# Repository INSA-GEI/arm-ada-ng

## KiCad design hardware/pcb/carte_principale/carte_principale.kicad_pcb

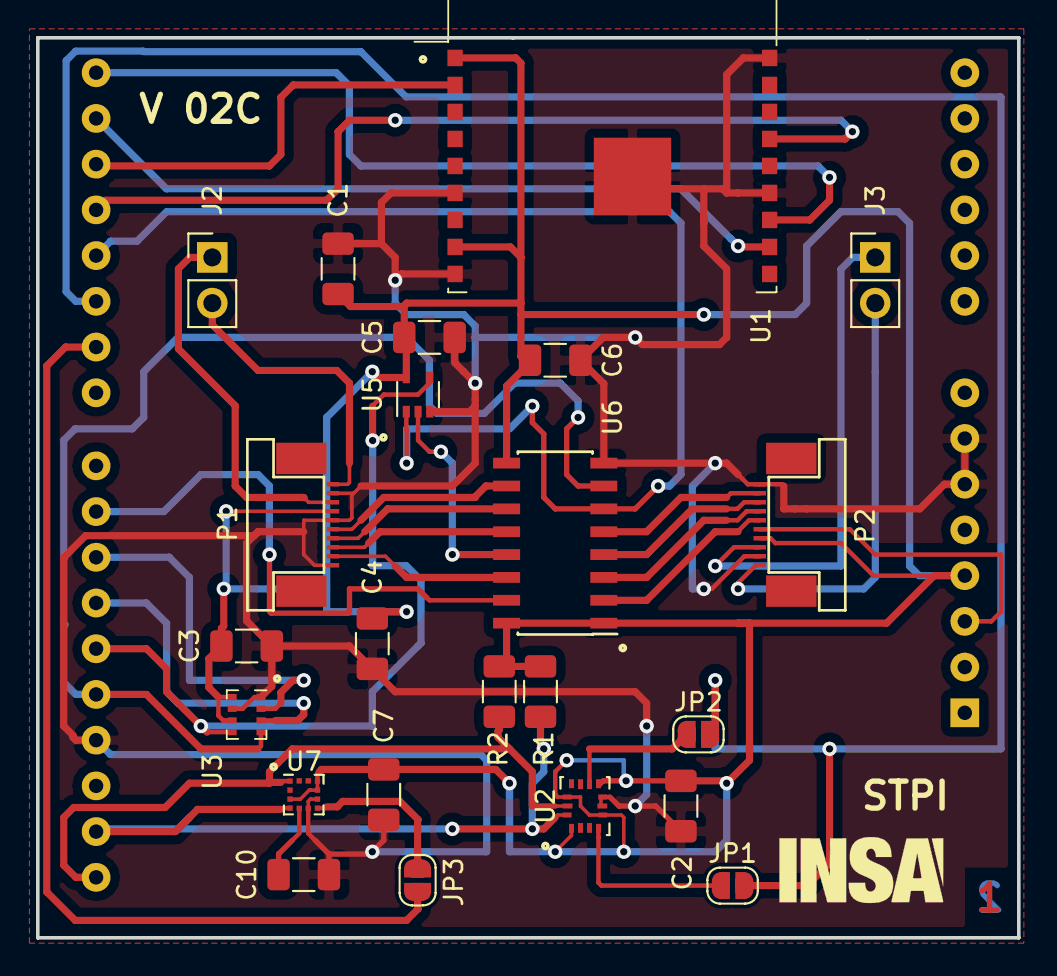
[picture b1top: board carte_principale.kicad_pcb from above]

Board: 2 copper layers, 54.5 x 50.0 mm, 25 parts (1 on the bottom side), 34 nets.

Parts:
C1, C2, C3, C4, C5, C6, C7: 100nF; C_1206_3216Metric
C10: 220nF; C_1206_3216Metric
J1: Arduino_UNO_R3; Arduino_UNO_R3_Pin_Only
J2, J3: Conn_01x02; PinHeader_1x02_P2.54mm_Vertical
JP1, JP2, JP3: SJ; SolderJumper-2_P1.3mm_Open_RoundedPad1.0x1.5mm
Logo1: LOGO; insa-image
P1, P2: TE-FFC-10-0.5; FFC-10-0.5
R1, R2: 10K; R_1206_3216Metric
U1: ESP-WROOM-02
U2: LSM6DS3; LGA-14_3x2.5mm_P0.5mm_LayoutBorder3x4y-slim
U3: BMP280; Bosch_LGA-8_2x2.5mm_P0.65mm_ClockwisePinNumbering
U5: 74AHC1G125; SOT-353_SC-70-5
U6: 74LS166; SOIC-16_3.9x9.9mm_P1.27mm
U7: LIS2MDL; LGA-12_2x2mm_P0.5mm-slim

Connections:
/Audio_Left_1: J2.2, P1.10
/Audio_Left_2: J2.1, P1.8
/Audio_Right_1: J3.2, P2.10
/Audio_Right_2: J3.1, P2.8
/BMP280_EN: J1.25, U3.2
/I2C_SCL: J1.32, R2.2, U2.13, U7.1
/I2C_SDA: J1.31, R1.2, U2.14, U7.4
/KEYS_EN: J1.19, U5.1, U6.6
/KEYS_LOAD: J1.24, U6.15
/KEY_RST: J1.3, P2.6
/Key_A: P2.4, U6.3
/Key_B: P2.5, U6.2
/Key_Down: P1.2, U6.14
/Key_Left: P1.5, U6.10
/Key_Right: P1.4, U6.11
/Key_Up: P1.3, U6.12
/Key_X: P2.2, U6.5
/Key_Y: P2.3, U6.4
/LIS2MDL_IT: J1.21, JP3.1
/LSM6DS3_IT: J1.20, JP1.2, JP2.2
/SPI_MISO: J1.27, U3.5, U5.4
/SPI_MOSI: J1.26, U3.3
/SPI_SCK: J1.28, U3.4, U6.7
/WIFI_EN: J1.17, U1.2
/WIFI_RST: J1.18, U1.15
/WIFI_RX: J1.16, U1.11
/WIFI_TX: J1.15, U1.12
GND: C1.2, C2.2, C3.2, C4.2, C5.2, C6.2, C7.2, C10.2, J1.6, J1.7, J1.29, P1.1, P1.6, P1.9, P2.1, P2.9, U1.6, U1.9, U1.13, U1.18, U1.19, U2.6, U2.7, U3.1, U3.7, U5.3, U6.8, U7.6, U7.8
unnamed: C10.1, U7.5
unnamed: JP1.1, U2.4
unnamed: JP2.1, U2.9
unnamed: JP3.2, U7.7
unnamed: U5.2, U6.13
VCC: C1.1, C2.1, C3.1, C4.1, C5.1, C6.1, C7.1, J1.4, P1.7, P2.7, R1.1, R2.1, U1.1, U1.8, U2.1, U2.5, U2.8, U2.12, U3.6, U3.8, U5.5, U6.1, U6.9, U6.16, U7.3, U7.9, U7.10

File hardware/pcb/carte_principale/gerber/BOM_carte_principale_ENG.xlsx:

Part | Value | Device | Package | Description | Description2 | Qty | Place_YES/NO | Provided_by_customer_YES/NO | Distributor | Ordernumber | Weblink | Remarks_customer | Unit_price | Total_price | REMARKS_BETA | OPTION1 | OPTION2 | OPTION3
C3,C2,C7,C6,C1,C5,C4 | 100nF | C1206C104M5RACTU | 1206 | Capacitor, 100nf / 50V, X7R 1206 |  |  | YES | NO | MOUSER | 80-C1206C104M5R | https://www.mouser.fr/ProductDetail/80-C1206C104M5R
C10 | 220nF | C1206C224M5RACTU | 1206 | Capacitor, 220nf / 50V, X7R 1206 |  |  | YES | NO | MOUSER | 80-C1206C224M5R | https://www.mouser.fr/ProductDetail/80-C1206C224M5R
R1,R2 | 10K | RT1206FRD0710KL | 1206 | Resistor 10K 1206 |  |  | YES | NO | MOUSER | 603-RT1206FRD0710KL | https://www.mouser.fr/ProductDetail/603-RT1206FRD0710KL
U2 |  | LSM6DS3TR | LGA-14_3x2.5mm_P0.5mm | IMU 6DoF |  |  | YES | NO | MOUSER | 511-LSM6DS3TR | https://www.mouser.fr/ProductDetail/511-LSM6DS3TR
U3 |  | BMP280 | Bosch_LGA-8_2x2.5mm_P0.65mm | Pressure sensor |  |  | YES | NO | MOUSER | 262-BMP280 | https://www.mouser.fr/ProductDetail/262-BMP280
U5 |  | 74AHC1G125GW,125 | SOT-353 | Buffer 3-State |  |  | YES | NO | MOUSER | 771-74AHC1G125GW-G | https://www.mouser.fr/ProductDetail/771-74AHC1G125GW-G
U6 |  | 74HC166D,652 | SOIC-16 | Shift Register 8-BIT |  |  | YES | NO | MOUSER | 771-HC166D652 | https://www.mouser.fr/ProductDetail/771-HC166D652
U7 |  | LIS2MDLTR | LGA-12_2x2mm_P0.5mm | Hall sensor |  |  | YES | NO | FARNELL | 3129625 | https://fr.farnell.com/stmicroelectronics/lis2mdltr/magnetom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
P1,P2 |  | 1-1734592-0 | FFC-10-0.5 | Connector FFC/FCP 0,5mm pitch 10P |  |  | YES | NO | MOUSER | 571-1-1734592-0 | https://www.mouser.fr/ProductDetail/571-1-1734592-0
J1 |  |  |  | Arduino footprint |  |  | NO | NO
J2,J3 |  |  |  | Two pins header |  |  | NO | NO
U1 |  |  |  | ESP32-WROOM |  |  | NO | NO
JP1,JP2,JP3 |  |  |  | Jumper |  |  | NO | NO

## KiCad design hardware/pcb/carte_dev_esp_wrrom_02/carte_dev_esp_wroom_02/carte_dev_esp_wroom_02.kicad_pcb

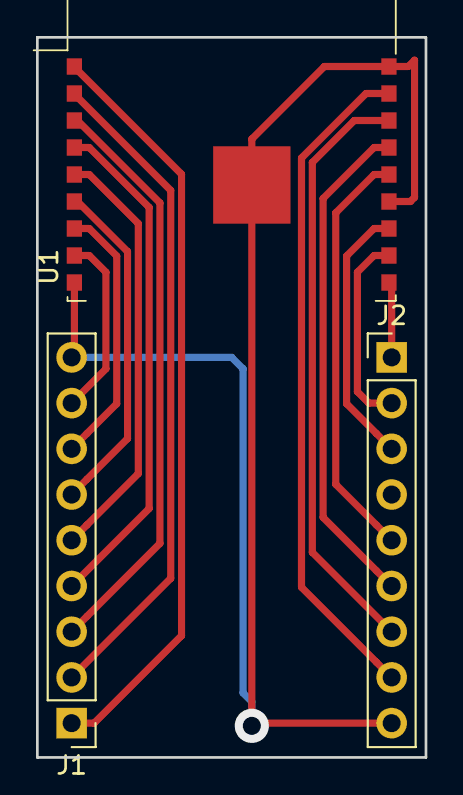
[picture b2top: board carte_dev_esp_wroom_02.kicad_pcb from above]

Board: 2 copper layers, 21.6 x 40.0 mm, 3 parts (0 on the bottom side), 16 nets.

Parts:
J1, J2: Conn_01x09; PinHeader_1x09_P2.54mm_Vertical
U1: ESP-WROOM-02

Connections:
+3V3: J1.1, U1.1
GND: J1.9, J2.9, U1.9, U1.13, U1.18, U1.19
unnamed: J1.2, U1.2
unnamed: J1.3, U1.3
unnamed: J1.4, U1.4
unnamed: J1.5, U1.5
unnamed: J1.6, U1.6
unnamed: J1.7, U1.7
unnamed: J1.8, U1.8
unnamed: J2.1, U1.10
unnamed: J2.2, U1.11
unnamed: J2.3, U1.12
unnamed: J2.5, U1.14
unnamed: J2.6, U1.15
unnamed: J2.7, U1.16
unnamed: J2.8, U1.17

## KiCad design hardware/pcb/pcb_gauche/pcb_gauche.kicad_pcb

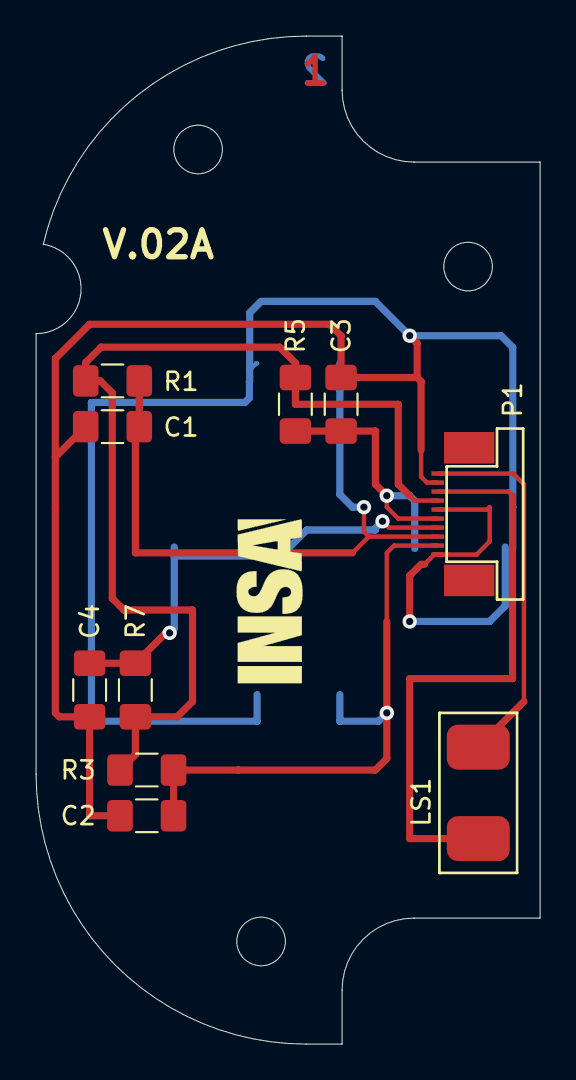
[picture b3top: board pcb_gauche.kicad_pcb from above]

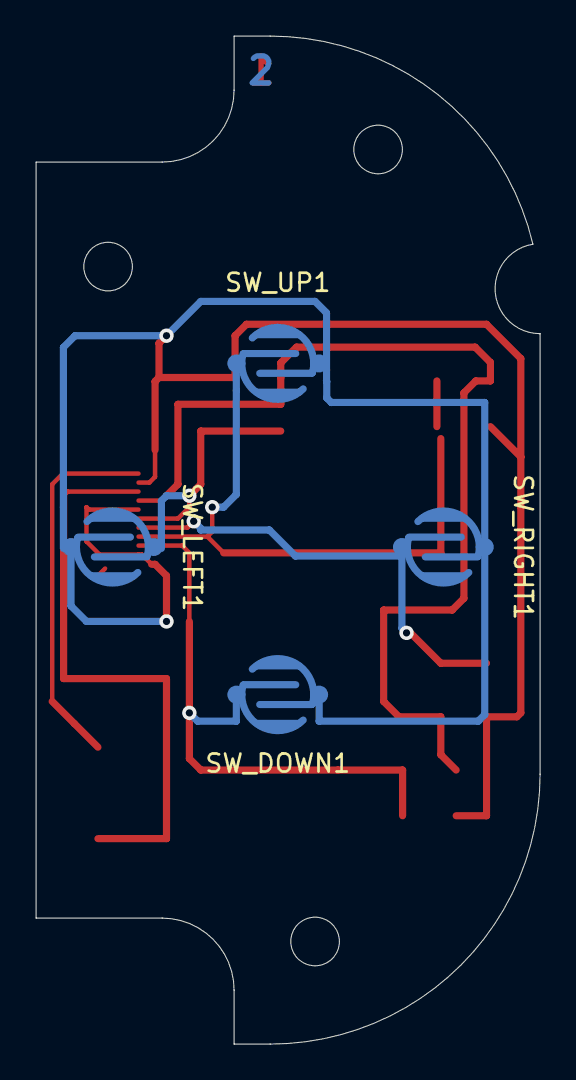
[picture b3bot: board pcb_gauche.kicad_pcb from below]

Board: 2 copper layers, 28.0 x 56.0 mm, 15 parts (4 on the bottom side), 8 nets.

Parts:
C1, C2, C3, C4: C; C_1206_3216Metric_Pad1.42x1.75mm_HandSolder
LS1: Speaker
Logo1: LOGO; insa-image
P1: TE-FFC-10-0.5; FFC-10-0.5
R1, R3, R5, R7: R; R_1206_3216Metric_Pad1.42x1.75mm_HandSolder
SW_DOWN1: SW_Push; RubberKey-4mm-2
SW_LEFT1: SW_Push; RubberKey-4mm-2
SW_RIGHT1: SW_Push; RubberKey-4mm-2
SW_UP1: SW_Push; RubberKey-4mm-2

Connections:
/Audio_Left_1: LS1.1, P1.1
/Audio_Left_2: LS1.2, P1.3
/Key_Down: C2.1, P1.9, R3.2, SW_DOWN1.2
/Key_Left: C3.1, P1.6, R5.2, SW_LEFT1.2
/Key_Right: C4.1, P1.7, R7.2, SW_RIGHT1.2
/Key_Up: C1.1, P1.8, R1.2, SW_UP1.2
GND: C1.2, C2.2, C3.2, C4.2, P1.2, P1.5, P1.10, SW_DOWN1.1, SW_LEFT1.1, SW_RIGHT1.1, SW_UP1.1
VCC: P1.4, R1.1, R3.1, R5.1, R7.1

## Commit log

2018-07-13 Initial release
2018-08-20 nouvelles branches
2018-08-20 nouvelle branche stable
2018-08-20 suppression des fichiers chm
2018-08-20 branche master
2018-10-01 Add extensions boards projects
2019-02-07 Synchro des dernieres modifs
2019-02-08 Correction de l'estimation des couts + Edition d'un devis chez Mouser
2019-02-08 petite coquille dans le devis
2019-02-27 ajout du pcb de la carte principale
2019-03-14 ajout des pcb gauche et droit
2019-04-05 Modifications des fonts et debut de la creation du drivers de touches
2019-04-18 ajout du wifi (debut) et mise a jour pcb
2019-04-19 Ajout d'une version slim de la gameboy
2019-04-23 - Mise a jour du boitier - Reorganisation des devis et estimations
2019-04-23 -- Export des pcb gauche et droit au format DXF pour importation sous Kicad
2019-04-26 mise a jour des pcb et design mecaniques
2019-05-15 Reprise du code du firmware
2019-05-17 Commit de sauvegarde
2019-06-03 sauvegarde intermediaire
2019-06-14 Version a peu pres fonctionnelle des drivers
2019-06-19 - Ajout de l'export STL de la nouvelle face avant
2019-06-19 reorganisation des fichiers du firmware
2019-06-24 reprise du mapping memoire
2019-06-24 Correction de la partie legacy
2019-06-28 premiere version qui commence a marcher
2019-07-16 synthe passé en 16 bits et fonctionnele
2019-07-17 retour au 8 bits pour le synthe => compatibilité avec l'ancienne gameboy
2019-09-05 Legere modification sur la face avant et la face arriere suite au retour de WEERG
2019-09-10 mise a jour devis pour STPI+ ajout des fichiers de cache pour PCB kicad
2019-09-10 Version 1.0-LEGACY terminée
2019-09-18 generation des fichiers gerber pour assemblage de la carte principale
2020-05-13 Essai d'execution en SDRAM
2020-05-14 - mise en place du lanceur TouchGFX
2020-05-14 Sauvegarde du projet 'execution en Ram'
2020-05-19 Premier jet de l'IHM nouvelle generation
2020-06-02 Demarrage de la doc technique
2020-06-23 mise a jour de l'IHM + docs
2020-09-15 commit avant changement de branche
2020-09-18 Conversion du projet en gnatstudio
2020-09-22 truc qui marche enfin
2020-10-12 Premiere version qui marche
2020-10-12 Nettoyage
2020-10-15 reorganisation des repertoire + portage des Tp en cours
2020-10-16 Fin du portage pour profil zfp
2021-03-26 commit avant basculement sur le depot arm-ada
